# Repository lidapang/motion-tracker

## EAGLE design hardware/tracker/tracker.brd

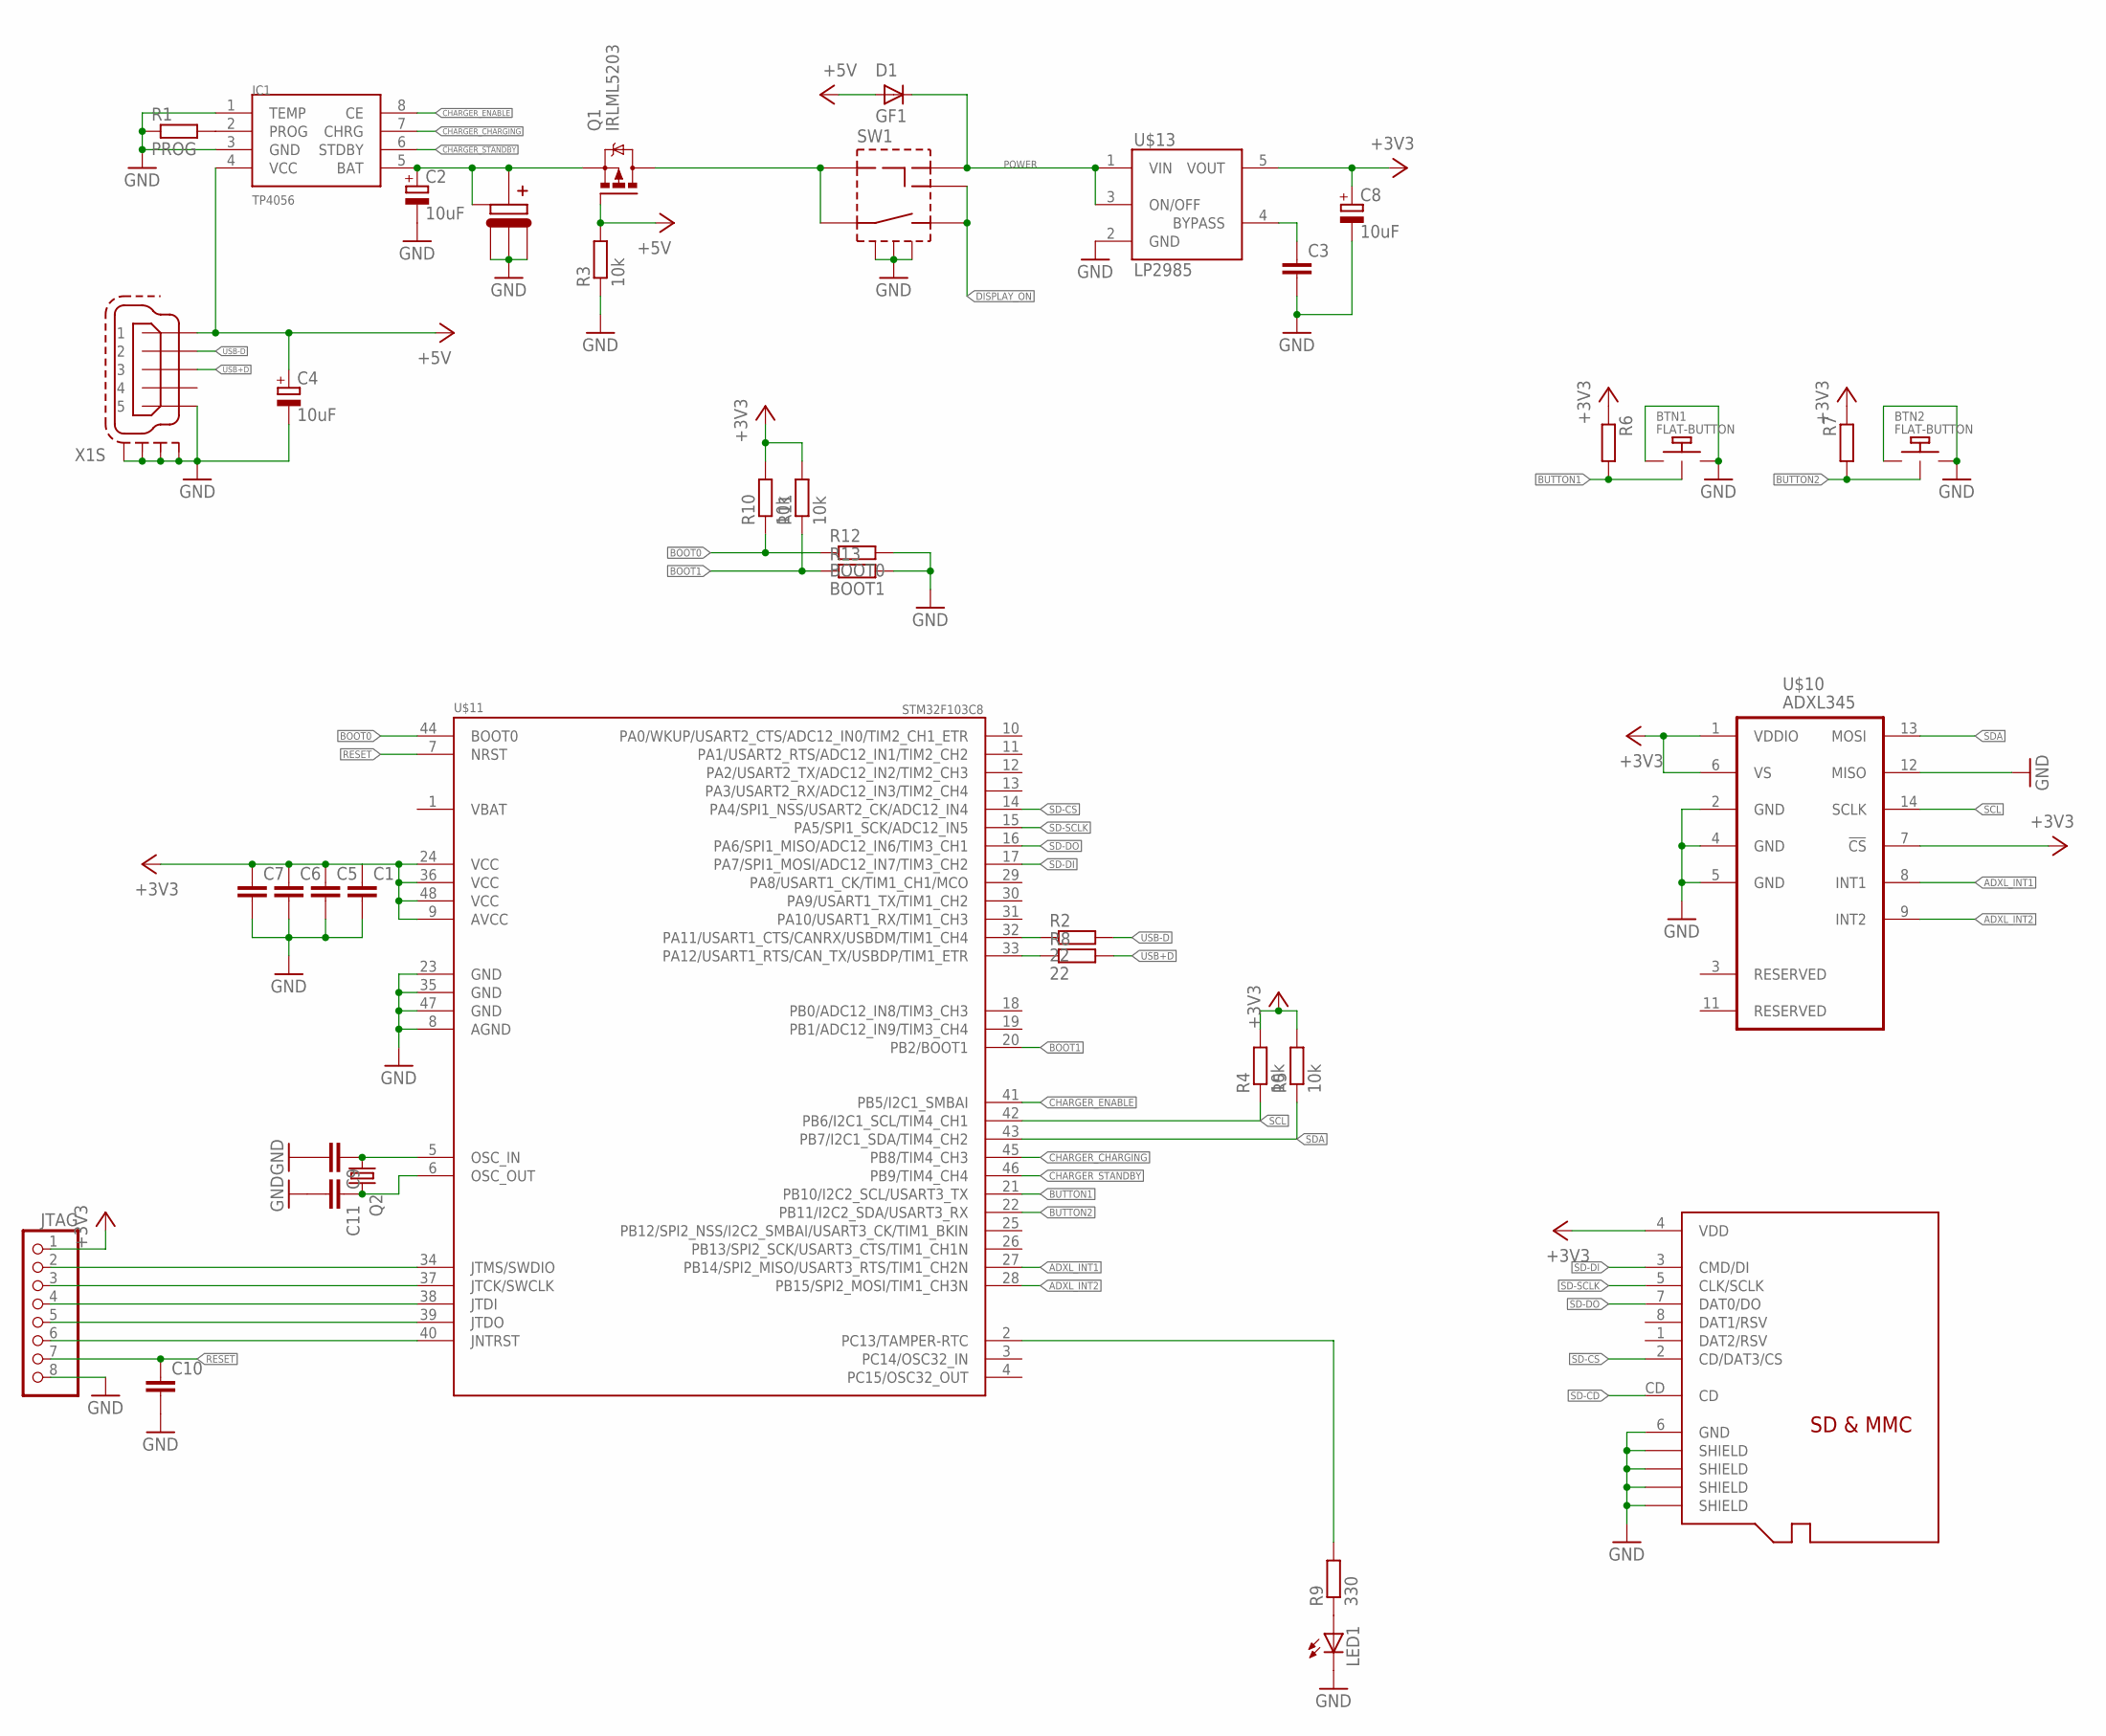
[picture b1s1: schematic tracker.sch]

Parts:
BTN1, BTN2: FLAT-BUTTON
C1, C3, C5, C6, C7, C9, C10, C11: C-EUC0805K; C0805K
C2, C4, C8: 10uF; B/3528-21W
D1: GF1; SMA-DO214AC
IC1: TP4056; SOP-8
JTAG: PINHD-1X8; PLL1.27-1X8
LED1: LEDSML1206; SML1206
Q1: IRLML5203; MICRO3
Q2: CRYSTALHC49S; HC49/S
R1: PROG; M0805
R2, R8: 22; R0805
R3, R4, R5, R10, R11: 10k; R0805
R6, R7: R-EU_R0805; R0805
R9: 330; R0805
R12: BOOT0; R0805
R13: BOOT1; R0805
SW1: PWR-SWITCH
U$6: BATTERY+
U$7: BATTERY-
U$10: ADXL345; LGA14
U$11: STM32F103C8; LQFP48-7X7
U$12: MICROSD; C12075
U$13: LP2985AIM5-3.3; SOT25
X1: MINI-USB-SCHIELD-32005-301; 32005-301

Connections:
+3V3: C1.1, C5.1, C6.1, C7.1, C8.+, JTAG.1, R4.2, R5.2, R6.1, R7.1, R10.2, R11.2, U$10.1 (VDDIO), U$10.6 (VS), U$10.7 (!CS), U$11.9 (AVCC), U$11.24 (VCC), U$11.36 (VCC), U$11.48 (VCC), U$12.4 (VDD), U$13.5 (VOUT)
+5V: C4.+, D1.A, IC1.4 (VCC), Q1.1 (G), R3.2, X1.1
ADXL_INT1: U$10.8 (INT1), U$11.27 (PB14/SPI2_MISO/USART3_RTS/TIM1_CH2N)
ADXL_INT2: U$10.9 (INT2), U$11.28 (PB15/SPI2_MOSI/TIM1_CH3N)
BAT+: C2.+, IC1.5 (BAT), Q1.2 (S), U$6.PAD (BATTERY+#1), U$6.PIN (BATTERY+#2)
BAT-PROG: IC1.2 (PROG), R1.2
BOOT0: R10.1, R12.1, U$11.44 (BOOT0)
BOOT1: R11.1, R13.1, U$11.20 (PB2/BOOT1)
BUTTON1: BTN1.1 (2), R6.2, U$11.21 (PB10/I2C2_SCL/USART3_TX)
BUTTON2: BTN2.1 (2), R7.2, U$11.22 (PB11/I2C2_SDA/USART3_RX)
BYPASS: C3.1, U$13.4 (BYPASS)
CHARGER_CHARGING: IC1.7 (CHRG), U$11.45 (PB8/TIM4_CH3)
CHARGER_ENABLE: IC1.8 (CE), U$11.41 (PB5/I2C1_SMBAI)
CHARGER_STANDBY: IC1.6 (STDBY), U$11.46 (PB9/TIM4_CH4)
DISPLAY_ON: SW1.4 (BTN2), SW1.5 (PWR-OUT2)
GND: BTN1.2 (1), BTN1.3 (1), BTN2.2 (1), BTN2.3 (1), C1.2, C2.-, C3.2, C4.-, C5.2, C6.2, C7.2, C8.-, C9.2, C10.2, C11.2, IC1.1 (TEMP), IC1.3 (GND), JTAG.8, LED1.C, R1.1, R3.1, R12.2, R13.2, SW1.SCREEN@1 (SHIELD), SW1.SCREEN@2 (SHIELD), SW1.SCREEN@3 (SHIELD), U$7.P$1, U$7.P$2, U$7.P$3, U$10.2 (GND), U$10.4 (GND), U$10.5 (GND), U$10.12 (MISO), U$11.8 (AGND), U$11.23 (GND), U$11.35 (GND), U$11.47 (GND), U$12.6 (GND), U$12.GND@1 (SHIELD), U$12.GND@2 (SHIELD), U$12.GND@3 (SHIELD), U$12.GND@4 (SHIELD), U$13.2 (GND), X1.5, X1.M1 (S1), X1.M2 (S2), X1.M3 (S3), X1.M4 (S4)
unnamed: Q1.3 (D), SW1.1 (BTN1), SW1.2 (PWR-IN)
unnamed: C9.1, Q2.1, U$11.5 (OSC_IN)
unnamed: C11.1, Q2.2, U$11.6 (OSC_OUT)
unnamed: R2.1, U$11.32 (PA11/USART1_CTS/CANRX/USBDM/TIM1_CH4)
unnamed: R8.1, U$11.33 (PA12/USART1_RTS/CAN_TX/USBDP/TIM1_ETR)
unnamed: LED1.A, R9.1
unnamed: JTAG.2, U$11.34 (JTMS/SWDIO)
unnamed: R9.2, U$11.2 (PC13/TAMPER-RTC)
unnamed: JTAG.3, U$11.37 (JTCK/SWCLK)
unnamed: JTAG.4, U$11.38 (JTDI)
unnamed: JTAG.5, U$11.39 (JTDO)
unnamed: JTAG.6, U$11.40 (JNTRST)
POWER: D1.K (C), SW1.3 (PWR-OUT1), U$13.1 (VIN), U$13.3 (ON/OFF)
RESET: C10.1, JTAG.7, U$11.7 (NRST)
SCL: R4.1, U$10.14 (SCLK), U$11.42 (PB6/I2C1_SCL/TIM4_CH1)
SD-CD: U$12.CD
SD-CS: U$11.14 (PA4/SPI1_NSS/USART2_CK/ADC12_IN4), U$12.2 (CD/DAT3/CS)
SD-DI: U$11.17 (PA7/SPI1_MOSI/ADC12_IN7/TIM3_CH2), U$12.3 (CMD/DI)
SD-DO: U$11.16 (PA6/SPI1_MISO/ADC12_IN6/TIM3_CH1), U$12.7 (DAT0/DO)
SD-SCLK: U$11.15 (PA5/SPI1_SCK/ADC12_IN5), U$12.5 (CLK/SCLK)
SDA: R5.1, U$10.13 (MOSI), U$11.43 (PB7/I2C1_SDA/TIM4_CH2)
USB+D: R8.2, X1.3
USB-D: R2.2, X1.2
VBAT: U$11.1 (VBAT)

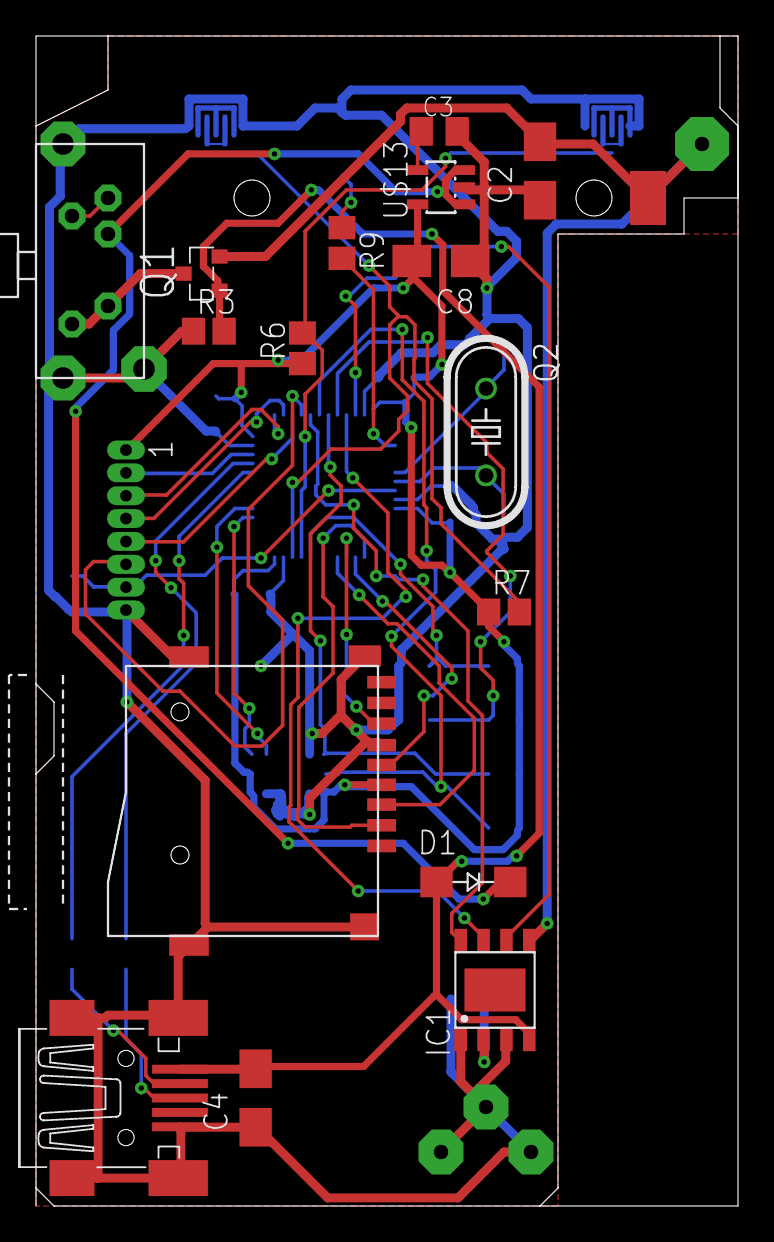
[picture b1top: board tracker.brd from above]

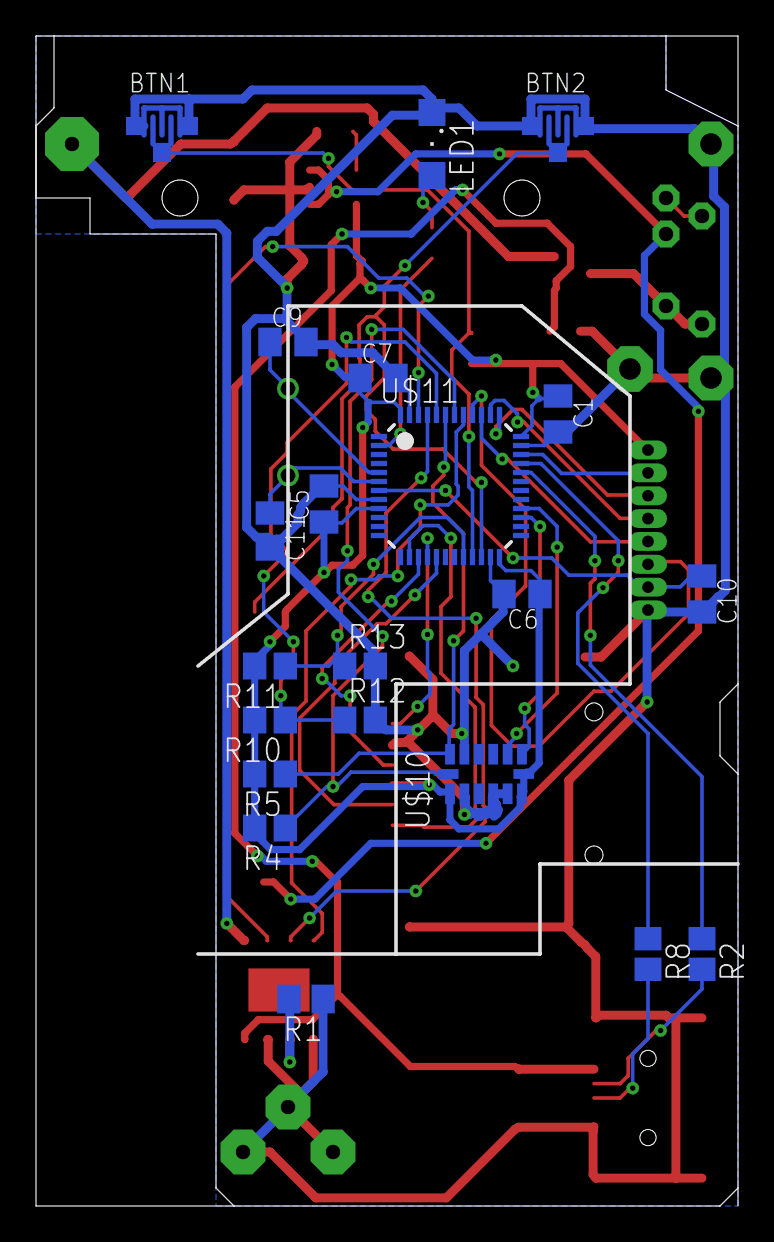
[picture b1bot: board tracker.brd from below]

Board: 2 copper layers, 39.0 x 65.0 mm, 40 parts (21 on the bottom side), 38 nets.

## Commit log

2014-02-05 Created EAGLE project
2014-02-05 Parts libraries started
2014-02-05 FGPMMOPA6C GPS Standalone Module added
2014-02-05 Added KCSA02 and KCSC02 LED modules
2014-02-06 no message
2014-03-01 Board version 1
2014-03-18 Rev A board
2014-04-26 CooCox project
2014-04-26 Updated gitignore
